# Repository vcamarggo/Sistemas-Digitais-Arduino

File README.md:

# Avaliações da disciplina de Sistemas Digitais - 2017
Qualquer reprodução do mesmo, de forma parcial ou integral deve ser comunicada ao professor.

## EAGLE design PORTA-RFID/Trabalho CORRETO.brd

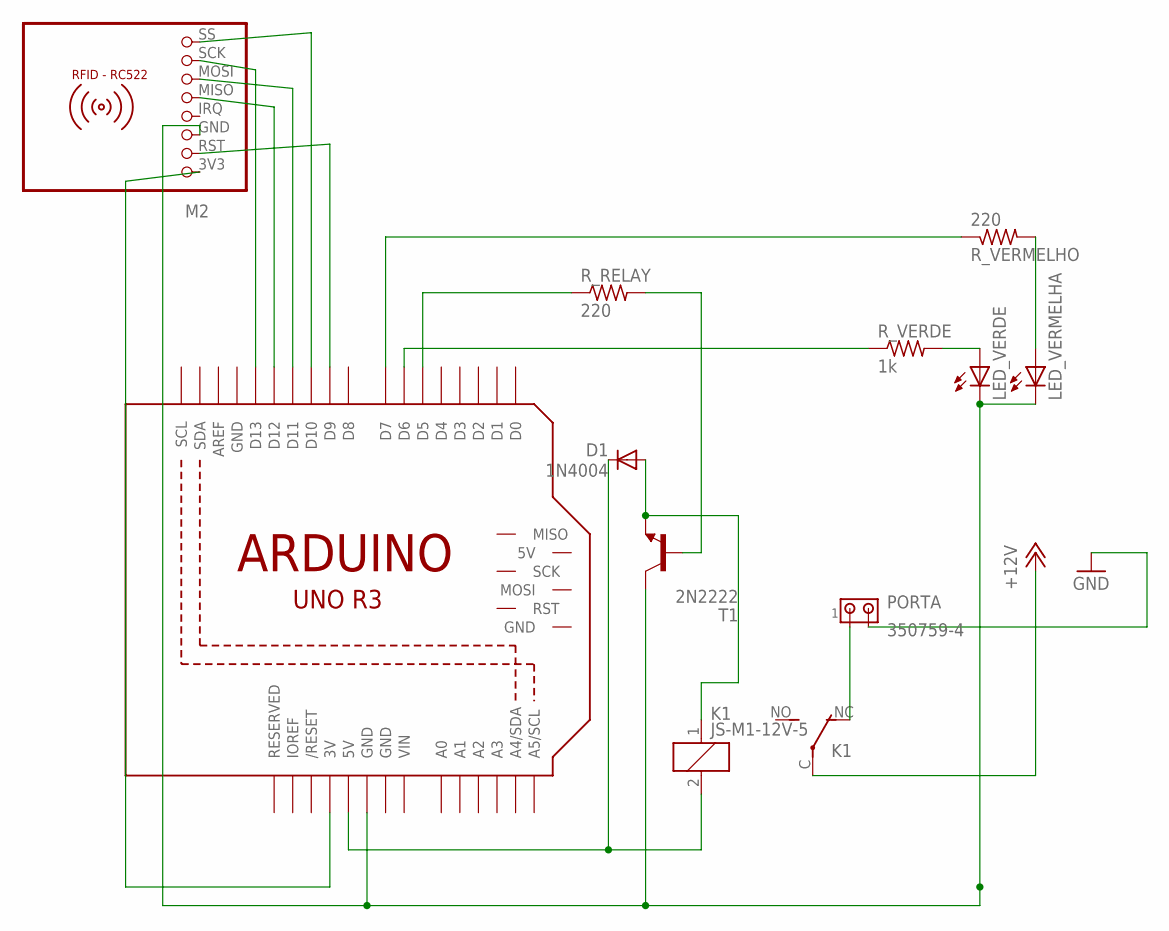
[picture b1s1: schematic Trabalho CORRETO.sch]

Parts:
D1: 1N4004; DO41-10
K1: JS-M1-12V-5; JS-M
LED_VERDE: LED5MM
LED_VERMELHA: LED5MM
M1: ARDUINO_R3_ICSP; ARDUINOR3_ICSP
M2: RFID-RC522
PORTA: 350759-4
R_RELAY: 220; 0204/5
R_VERDE: 1k; 0204/5
R_VERMELHO: 220; 0204/5
T1: 2N2222; TO92-EBC-OVAL

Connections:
3.3V: M1.3V, M2.3V3 (1)
+12V: K1.C
D6: M1.D6, R_VERDE.1
D7: M1.D7, R_VERMELHO.1
D9: M1.D9, M2.RST (2)
D10: M1.D10, M2.SS (8)
D11: M1.D11, M2.MOSI (6)
D12: M1.D12, M2.MISO (5)
D13: M1.D13, M2.SCK (7)
GND: LED_VERDE.K (C), LED_VERMELHA.K (C), M1.GND, M1.GND@1 (GND), M1.GND@3 (GND), M2.GND (3), PORTA.2, T1.C
unnamed: R_RELAY.2, T1.B
unnamed: LED_VERDE.A, R_VERDE.2
unnamed: LED_VERMELHA.A, R_VERMELHO.2
unnamed: D1.C, K1.2, M1.5V
unnamed: M1.D5, R_RELAY.1
unnamed: D1.A, K1.1, T1.E
unnamed: K1.NC (O), PORTA.1
VIN: M1.VIN

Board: 2 copper layers, 11 parts (0 on the bottom side), 16 nets, no tracks yet.

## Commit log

2017-06-18 Commit inicial sistemas de arduino
2017-06-20 materiais de SD incluindo trabalho
2017-06-21 Correção da função login e melhoria das funções da biblitoteca
2017-06-24 Inserção das LEDs
2017-06-24 Adição de comentários
2017-07-12 Versão final
